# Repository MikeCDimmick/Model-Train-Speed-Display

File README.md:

# Model-Train-Speed-Display

Parts list:

10K resistor

HC-SR04 ultrasonic distance sensor

LSHD-5601 7-segment display x3

ATMEGA328p

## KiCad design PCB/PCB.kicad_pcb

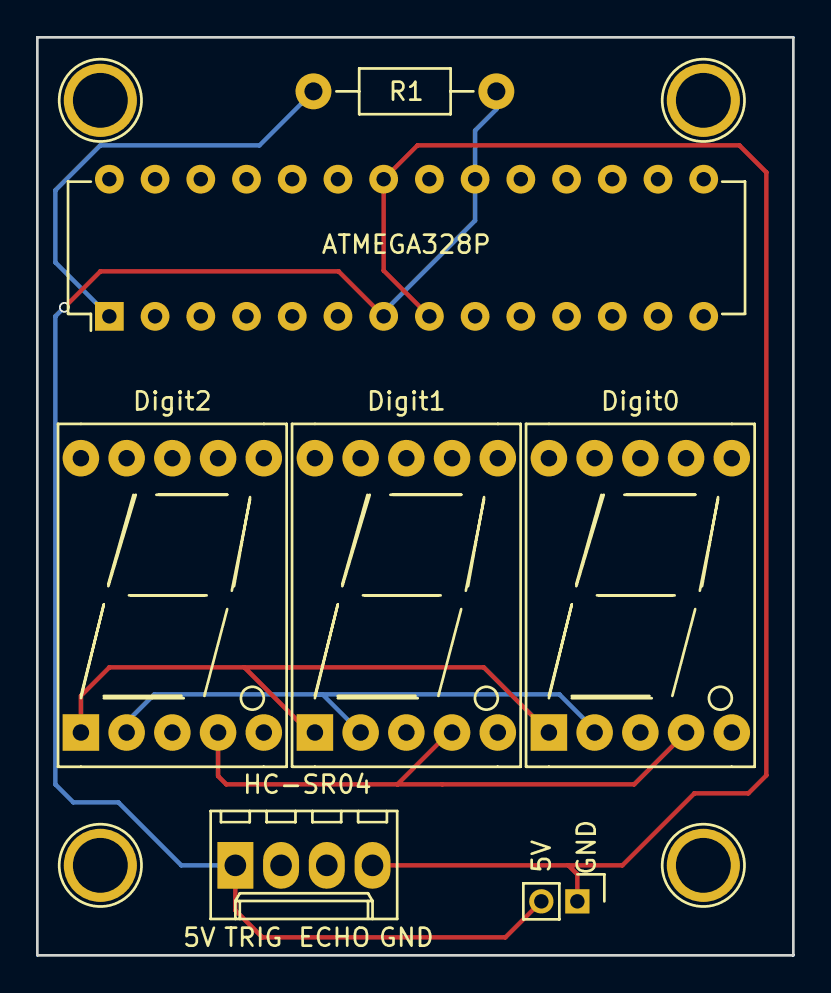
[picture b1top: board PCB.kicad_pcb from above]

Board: 2 copper layers, 42.0 x 51.0 mm, 6 parts (0 on the bottom side), 15 nets.

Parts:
ATMEGA328P: ATMEGA328-P; DIP-28_W7.62mm
Digit0, Digit1, Digit2: 7SEGMENTS; LSHD-5601
HC-SR04: HC-S04; Molex_KK-6410-04_04x2.54mm_Straight
R1: 10k; Resistor_Horizontal_RM10mm

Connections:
+5V: ATMEGA328P.7, ATMEGA328P.20, HC-SR04.1, R1.1
GND: ATMEGA328P.8, ATMEGA328P.22, HC-SR04.4
unnamed: ATMEGA328P.18, Digit0.1, Digit1.1, Digit2.1
unnamed: ATMEGA328P.17, Digit0.2, Digit1.2, Digit2.2
unnamed: ATMEGA328P.16, Digit0.4, Digit1.4, Digit2.4
unnamed: ATMEGA328P.15, Digit0.6, Digit1.6, Digit2.6
unnamed: ATMEGA328P.14, Digit0.7, Digit1.7, Digit2.7
unnamed: ATMEGA328P.2, Digit0.8
unnamed: ATMEGA328P.19, Digit0.9, Digit1.9, Digit2.9
unnamed: ATMEGA328P.9, Digit0.10, Digit1.10, Digit2.10
unnamed: ATMEGA328P.3, Digit1.8
unnamed: ATMEGA328P.4, Digit2.8
unnamed: ATMEGA328P.1, R1.2
unnamed: ATMEGA328P.5, HC-SR04.2
unnamed: ATMEGA328P.6, HC-SR04.3
